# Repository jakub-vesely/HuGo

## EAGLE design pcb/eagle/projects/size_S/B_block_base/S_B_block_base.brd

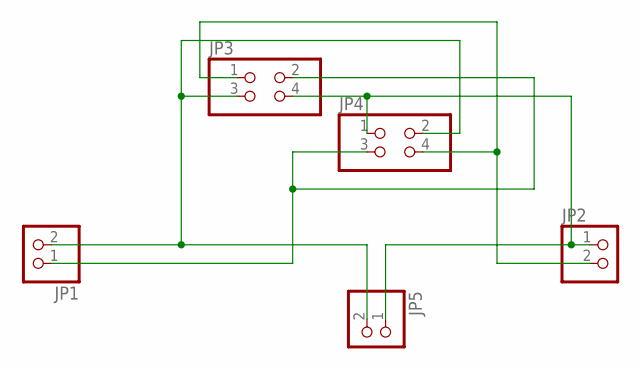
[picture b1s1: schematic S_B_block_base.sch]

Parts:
JP1, JP2, JP5: PINHD-1X2; 1X02
JP3, JP4: PINHD-2X2; 2X02

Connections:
GND: JP2.1, JP3.4, JP4.1, JP5.1
SCL: JP1.2, JP3.3, JP4.2, JP5.2
SDA: JP1.1, JP3.2, JP4.3
VDD: JP2.2, JP3.1, JP4.4

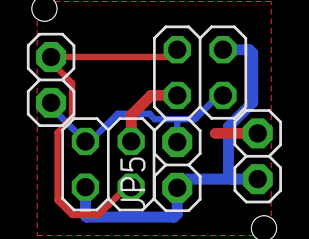
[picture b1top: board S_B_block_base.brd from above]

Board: 2 copper layers, 5 parts (0 on the bottom side), 4 nets.
